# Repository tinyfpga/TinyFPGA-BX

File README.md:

# TinyFPGA BX
The TinyFPGA BX board is a tiny FPGA board with low cost per logic element and convenient USB bitstream programming capability.  It measures just 18mm x 36mm and is a perfect fit for breadboards. The heart of the BX board is a iCE40LP8K-CM81 FPGA from Lattice.  

## Getting Started on the BX
The [TinyFPGA BX User Guide](https://tinyfpga.com/bx/guide.html) will help you get up and running with the BX. 

For full details on the ICE40 series of FPGAs you can read the [ICE40 Family Handbook](http://www.latticesemi.com/~/media/LatticeSemi/Documents/Handbooks/iCE40FamilyHandbook.pdf).

## Specifications
- Height: 1.4 inches, width: 0.7 inches
- Programming interface: USB 2.0 full-speed (12 mbit/sec)
- ICE40LP8K FPGA
    - 7,680 four-input look-up-tables
    - 128 KBit block RAM
    - Phase Locked Loop
    - 41 user IO pins
- 8 MBit of SPI Flash
- Onboard 3.3 V (300 mA) and 1.2 V (150 mA) LDO regulators
- Low-Power 16 MHz MEMs Oscillator
    - 1.3 mA power when active
    - 50 ppm stability.

## Project Directory Structure
### board
This contains a [KiCad](http://kicad.org/) project with the schematic and layout of the B-series boards.  The board is designed with 4/4mil track size/spacing and 0.2mm hole size.  BOM list for the BX board is available here as well.

### icecube2_template
This is a template iCEcube2 project for developing your own designs to program onto the board.  It takes care of pin and clock constraints.  Just edit the TinyFPGA_BX.v file to add your designs module(s).

### icestorm_template
This is a template IceStorm project for developing your own designs to program onto the board.  It takes care of pin and clock constraints.  Just edit the TinyFPGA_BX.v file to add your designs module(s).  Use `make` to build your project.

## Project Log
For more information on the development and production of the B-Series please read and follow the [TinyFPGA B-Series Project Page](https://hackaday.io/project/26848-tinyfpga-b-series) at hackaday.io.

## License
The TinyFPGA BX project is an open source project licensed under CERN Open Hardware Licence v1.2.  Please see the included LICENSE file for details.  If you do wish to distribute boards derived from this open source hardware project then you must also release the source files for the boards under CERN Open Hardware Licence v1.2.  You are free to do this, but please improve upon the original design and provide a tangible benefit for users of the board.

## Building your own TinyFPGA BX Board
It is possible to build the TinyFPGA BX boards by hand in a home lab.  However, it uses tiny 0402 surface mount capacitors and resistors and the iCE40 FPGAs used are in a 81 ball BGA package with 0.4mm pitch between the balls.  It is a challenging undertaking and will most likely result in some bad assembled boards along with the good.  I have used the following with success to hand assemble the prototype boards:
+ Parts for the [TinyFPGA BX](https://octopart.com/bom-tool/ALrZVouf)
+ [Lead-Free Solder Paste](https://www.amazon.com/gp/product/B00HKK6XHC)
+ [Stainless Steel Solder Paste Squeegee](http://dirtypcbs.com/store/details/14/solder-paste-squeegee)
+ [TinyFPGA BX Solder Paste Stencil](https://www.oshstencils.com)
  + You'll need to generate the gerber files and upload the solder paste layer.  If you plan on using solder paste for the FPGA chip, you will want the stainless steel stencil, I do not believe the polymide will work with the fine pitch BGA package.  I have found that fine-pitch BGA packages are easier to assemble with only flux and no paste for prototypes.
+ [TinyFPGA BX PCBs](https://oshpark.com/shared_projects/uMrRTfyL)
  + OSH Park does a very nice job with these boards on their 4-layer process.
+ [Precision Tweezers](https://www.amazon.com/Precision-Anti-static-Marrywindix-Electronics-Jewelry-making/dp/B00DVIEJ14) for placing parts on the board
+ Some sort of magnifying tool for placing parts ([magnifying glasses](https://www.amazon.com/dp/B01H8808H6), [magnifying lamp](https://www.amazon.com/Brightech-LightView-SuperBright-Magnifier-Adjustable/dp/B00UW2IRJ2), microscope)
+ [Reflow Oven](http://www.whizoo.com/)
  + This is the kit I use to reflow my prototypes.  You may also be able to use a good hot-plate or hot-air tool.
+ [Lattice FPGA Programmer](https://www.ebay.com/sch/i.html?_productid=533163279)
  + You will need this to load the bootloader onto the SPI Flash.  Once the bootloader is installed you can use the Python-based programmer application to program the board over USB.

## Buy TinyFPGA BX Boards
If you don't want to go through the hassle of ordering parts, tools, and supplies and assembling the boards yourself you can order professionally assembled and tested boards from [Crowd Supply](https://www.crowdsupply.com/tinyfpga/tinyfpga-bx).  These boards are not hobbyist-made, they are fabricated and assembled in a professional PCB fab that manufactures and assembles many other consumer, industrial and military electronics.  They go through an automated testing and programming process to ensure the board is healthy and ready to program over USB.  When the Crowd Supply campaign ends and all the backers orders are shipped the boards will become available on Tindie and the TinyFPGA Store.

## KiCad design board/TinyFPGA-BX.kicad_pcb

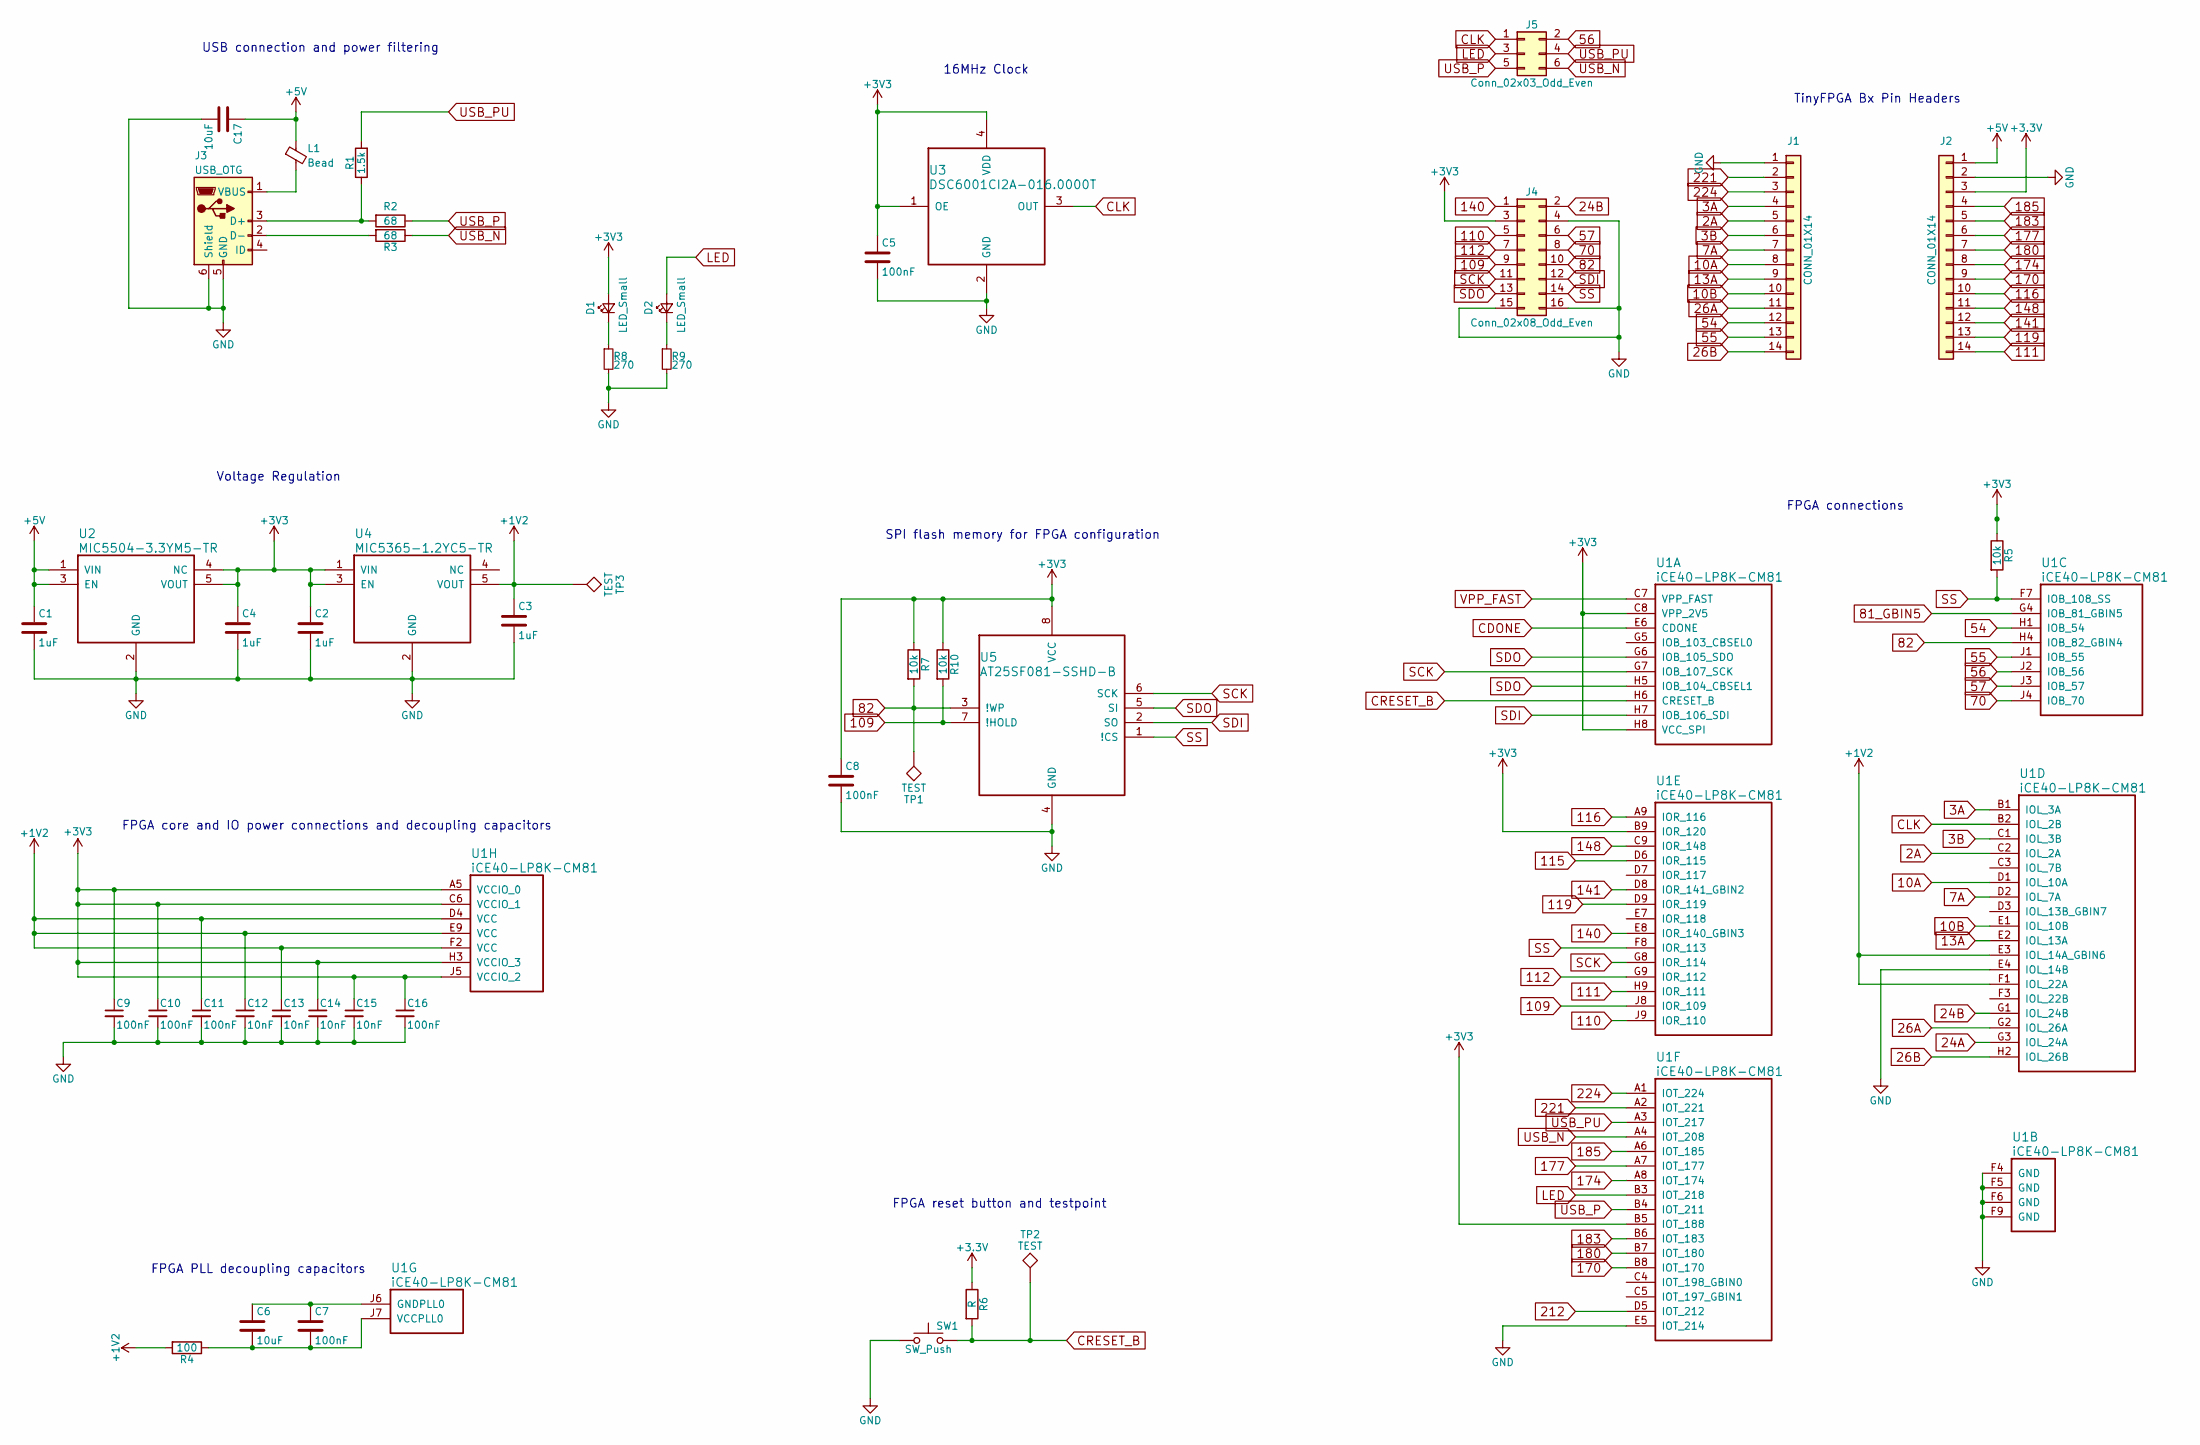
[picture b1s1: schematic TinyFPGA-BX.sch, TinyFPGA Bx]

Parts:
C1, C2, C3, C4: 1uF; C_0402_NoSilk
C5, C7, C8, C9, C10, C11, C16: 100nF; C_0402_NoSilk
C6, C17: 10uF; C_0603
C12, C13, C14, C15: 10nF; C_0402_NoSilk
D1, D2: LED_Small; LED_0603
J1, J2: CONN_01X14; Pin_Header_Straight_1x14_Pitch2.54mm
J3: USB_OTG; USB_Micro-B
J4: Conn_02x08_Odd_Even; Pin_Header_Straight_2x08_Pitch2.54mm_SMD
J5: Conn_02x03_Odd_Even; Pin_Header_Straight_2x03_Pitch2.54mm_SMD
L1: Bead; L_0603
R1: 1.5k; R_0402_NoSilk
R2, R3: 68; R_0402_NoSilk
R4: 100; R_0402_NoSilk
R5, R7, R10: 10k; R_0402_NoSilk
R6: R; R_0402
R8, R9: 270; R_0402_NoSilk
SW1: SW_Push; PTS_810_SMT_Switch
TP1, TP2, TP3: TEST; Measurement_Point_Round-SMD-Pad_Small
U1: iCE40-LP8K-CM81; CM81
U2: MIC5504-3.3YM5-TR; SC-70-C5
U3: DSC6001CI2A-016.0000T; CDFN3225-4LD-PL-1
U4: MIC5365-1.2YC5-TR; SC-70-C5
U5: AT25SF081-SSHD-B; SOIC-8-1EP_3.9x4.9mm_Pitch1.27mm

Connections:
2A: J1.5, U1.C2 (IOL_2A)
3A: J1.4, U1.B1 (IOL_3A)
3B: J1.6, U1.C1 (IOL_3B)
7A: J1.7, U1.D2 (IOL_7A)
10A: J1.8, U1.D1 (IOL_10A)
10B: J1.10, U1.E1 (IOL_10B)
13A: J1.9, U1.E2 (IOL_13A)
24A: U1.G3 (IOL_24A)
24B: J4.2, U1.G1 (IOL_24B)
26A: J1.11, U1.G2 (IOL_26A)
26B: J1.14, U1.H2 (IOL_26B)
54: J1.12, U1.H1 (IOB_54)
55: J1.13, U1.J1 (IOB_55)
56: J5.2, U1.J2 (IOB_56)
57: J4.6, U1.J3 (IOB_57)
70: J4.8, U1.J4 (IOB_70)
81_GBIN5: U1.G4 (IOB_81_GBIN5)
82: J4.10, R7.2, TP1.1, U1.H4 (IOB_82_GBIN4), U5.3 (!WP)
109: J4.9, R10.2, U1.J8 (IOR_109), U5.7 (!HOLD)
110: J4.5, U1.J9 (IOR_110)
111: J2.14, U1.H9 (IOR_111)
112: J4.7, U1.G9 (IOR_112)
115: U1.D6 (IOR_115)
116: J2.10, U1.A9 (IOR_116)
119: J2.13, U1.D9 (IOR_119)
140: J4.1, U1.E8 (IOR_140_GBIN3)
141: J2.12, U1.D8 (IOR_141_GBIN2)
148: J2.11, U1.C9 (IOR_148)
170: J2.9, U1.B8 (IOT_170)
174: J2.8, U1.A8 (IOT_174)
177: J2.6, U1.A7 (IOT_177)
180: J2.7, U1.B7 (IOT_180)
183: J2.5, U1.B6 (IOT_183)
185: J2.4, U1.A6 (IOT_185)
212: U1.D5 (IOT_212)
221: J1.2, U1.A2 (IOT_221)
224: J1.3, U1.A1 (IOT_224)
+1V2: C3.1, C11.1, C12.1, C13.1, R4.2, TP3.1, U1.D4 (VCC), U1.E3 (IOL_14A_GBIN6), U1.E9 (VCC), U1.F1 (IOL_22A), U1.F2 (VCC), U4.5 (VOUT)
+5V: C1.1, C17.1, J2.1, L1.1, U2.1 (VIN), U2.3 (EN)
CDONE: U1.E6 (CDONE)
CLK: J5.1, U1.B2 (IOL_2B), U3.3 (OUT)
CRESET_B: R6.2, SW1.2, TP2.1, U1.H6 (CRESET_B)
GND: C1.2, C2.2, C3.2, C4.2, C5.2, C8.2, C9.2, C10.2, C11.2, C12.2, C13.2, C14.2, C15.2, C16.2, C17.2, J1.1, J2.2, J3.5 (GND), J3.6 (Shield), J4.4, J4.15, J4.16, R8.2, R9.2, SW1.1, U1.E4 (IOL_14B), U1.E5 (IOT_214), U1.F4 (GND), U1.F5 (GND), U1.F6 (GND), U1.F9 (GND), U2.2 (GND), U3.2 (GND), U4.2 (GND), U5.4 (GND)
LED: D2.2 (A), J5.3, U1.B3 (IOT_218)
unnamed: C6.1, C7.1, U1.J6 (GNDPLL0)
unnamed: C6.2, C7.2, R4.1, U1.J7 (VCCPLL0)
unnamed: D1.1 (K), R8.1
unnamed: D2.1 (K), R9.1
unnamed: J3.1 (VBUS), L1.2
unnamed: J3.2 (D-), R3.2
unnamed: J3.3 (D+), R1.1, R2.2
SCK: J4.11, U1.G7 (IOB_107_SCK), U1.G8 (IOR_114), U5.6 (SCK)
SDI: J4.12, U1.H7 (IOB_106_SDI), U5.2 (SO)
SDO: J4.13, U1.G6 (IOB_105_SDO), U1.H5 (IOB_104_CBSEL1), U5.5 (SI)
SS: J4.14, R5.2, U1.F7 (IOB_108_SS), U1.F8 (IOR_113), U5.1 (!CS)
USB_N: J5.6, R3.1, U1.A4 (IOT_208)
USB_P: J5.5, R2.1, U1.B4 (IOT_211)
USB_PU: J5.4, R1.2, U1.A3 (IOT_217)
VPP_FAST: U1.C7 (VPP_FAST)

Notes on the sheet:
FPGA core and IO power connections and decoupling capacitors
FPGA PLL decoupling capacitors
USB connection and power filtering
Voltage Regulation
16MHz Clock
SPI flash memory for FPGA configuration
FPGA reset button and testpoint
FPGA connections
TinyFPGA Bx Pin Headers

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
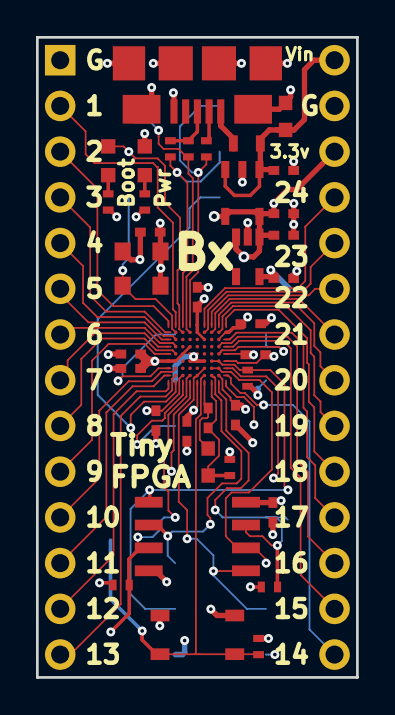
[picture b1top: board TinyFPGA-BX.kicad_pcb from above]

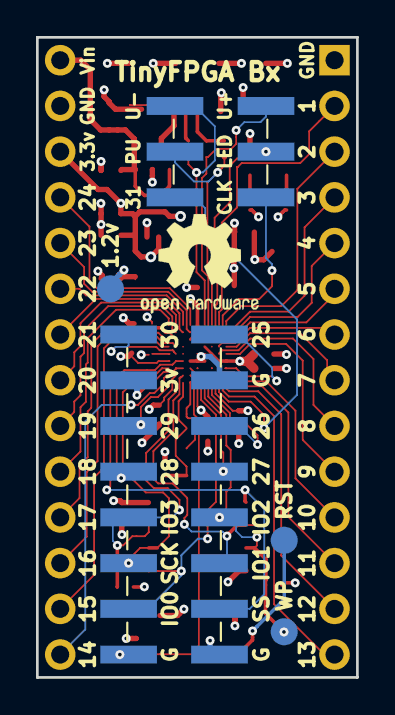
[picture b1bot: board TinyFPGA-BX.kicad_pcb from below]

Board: 4 copper layers, 17.8 x 35.6 mm, 44 parts (5 on the bottom side), 54 nets.

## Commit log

2018-03-30 first TinyFPGA BX commit after forking from B-series
2018-06-13 added apio temlpate
2018-06-13 adding apio install scripts
2018-07-13 Update icestorm project to match APIO project.
2018-07-23 add picosoc example with simple GPIO LED
2018-08-17 Update README.md
    Fix some markdown syntax
2018-08-18 Expose ENABLE_IRQ_QREGS to toplevel
2018-08-18 Add rule for creating firmware.hex
2018-08-18 Add top-level testbench
2018-08-18 Add FuseSoC .core file
2018-08-26 update icecube2 template to TinyFPGA_BX; it was TinyFPGA_B - Update pinout constraint file for TinyFPGA_BX - Update top level and clk constaints to correspond to updated pin names - Update project fi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
2018-09-16 Update apio_template
2018-09-16 Add iverilog in the install_apio scripts
2018-09-20 init globals and bss in start.S
2018-11-04 readme
2018-11-04 blinky firmwrae
2018-11-04 removed firmware.map
2018-11-04 added elf for simulation
2018-11-04 edits
2018-11-04 readme edits
2019-03-04 Regenerate TinyFPGA-BX schematics using the plot option.
    Regenerated the TinyFPGA-BX schematics the the plot option to allow
    searching of compoments in the schematics.
2019-07-08 Wrong model specified for icetime
    The picosoc sample Makefile had the wrong model specified. It is also incorrect stated that the TinyFPGA BX uses an HX8K in GoJimmyPi's blog post describing how to use picosoc on the TinyFPGA
    https://gojimmypi.blogspot.com/2019/01/risc-v-on-fpga-tinyfpga-via-wsl.html
2020-02-15 adding TinyFPGA BX reference card
2020-07-06 Switching to nextpnr since arachne-pnr is deprecated. Issue #23
2020-07-08 Switching picosoc to nextpnr
2020-07-08 Adding -mabi to allow it to compile with newer gcc
2021-11-08 Update README.md
    https://forum.kicad.info/t/warning-avoid-all-links-to-kicad-pcb-org-use-kicad-org/31521
2022-08-28 Move pin3_clk_16mhz to B2. Add user_led on B3.
2023-06-20 add simulation
2023-06-20 change directory structure
